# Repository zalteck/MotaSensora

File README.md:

# MotaSensora
Art monitoring for optimal conservation

This project was developed as the final degree job for my Telecommunications degree at the University of Granada. It implements from scratch a complete art monitoring system capable of measuring light, humidity, and temperature and ensuring that the values are kept in an acceptable range.

The system raises an alert in case any values get out of the safe range. It can also be escalated to control other devices in order to induce change to the monitored variables.

There are three different parts that form this project: Arduino code, Kicad files, and an Android app.

The Kicad files are used to build a PCB, used as an Arduino shield, that integrates the different sensors used in the project: Temperature, Humidity, and ambient light.

The Android app is completed and ready to install. With the app ArtSense, you will be able to communicate with the Arduino by Bluetooth, read the measurements, and know about the state of the ambient of the art piece, in terms of preventive conservation.

The Arduino code will manage the shield and read the sensors. It will also control Bluetooth connectivity and send the data to the Android device.
This is registered in zenodo:

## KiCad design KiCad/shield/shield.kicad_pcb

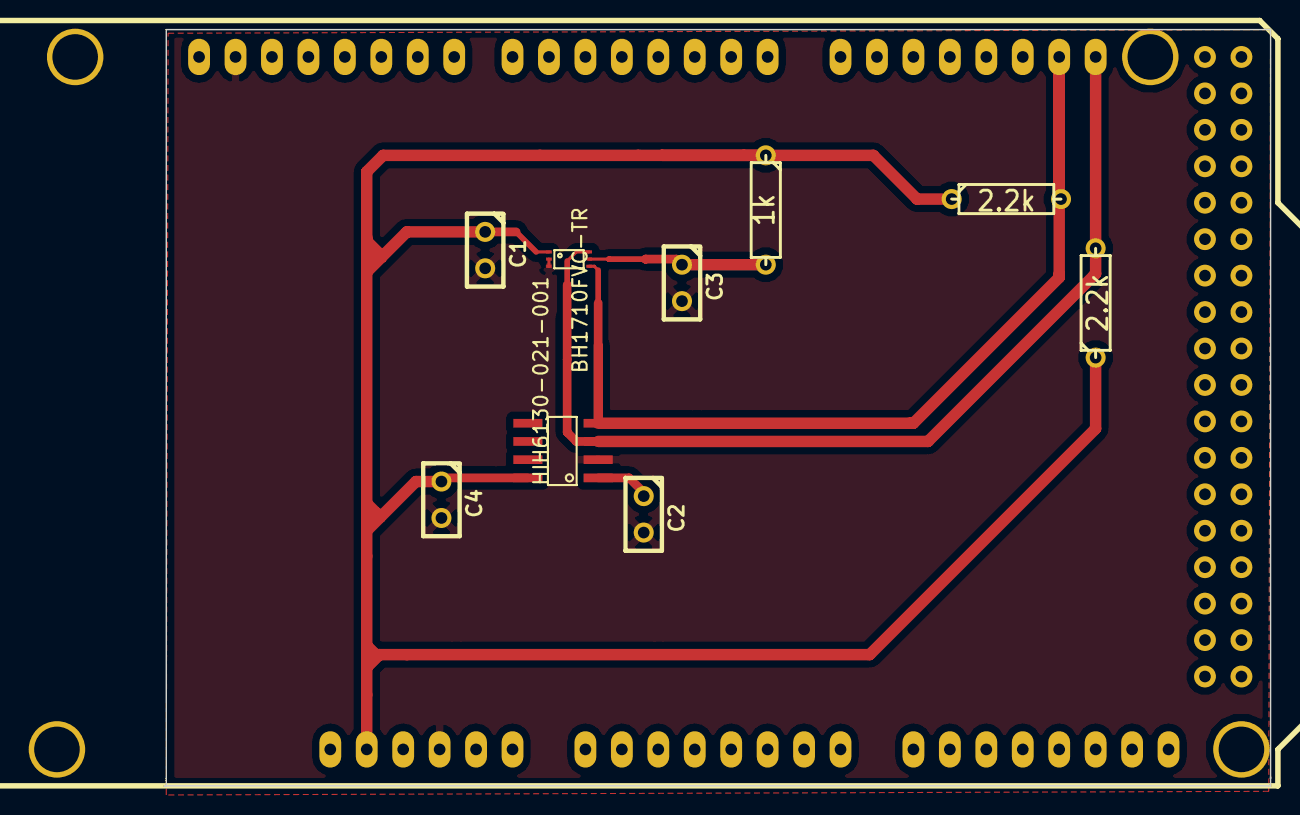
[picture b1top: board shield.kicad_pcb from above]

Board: 2 copper layers, 77.1 x 52.7 mm, 10 parts (0 on the bottom side), 6 nets.

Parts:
C1, C2: 0.1uF; C1
C3: 1uF; C1
C4: 0.22uF; C1
J1: BH1710FVC-TR; SensorLuz
J2: HIH6130-021-001; Humedad
R1: 1k; R3
R2, R3: 2.2k; R3
SHIELD1: ARDUINO_MEGA_SHIELD; ARDUINO MEGA SHIELD

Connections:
/DVI: C3.1, J1.5, R1.2
/SCL: J1.6, J2.3, R3.2, SHIELD1.21
/SDA: J1.4, J2.4, R2.2, SHIELD1.20
/Vcc: C1.1, C4.1, J1.1, J2.8, R1.1, R2.1, R3.1, SHIELD1.3V3
/Vcore: C2.1, J2.1
GND: C1.2, C2.2, C3.2, C4.2, J1.2, J1.3, J2.2, SHIELD1.GND1, SHIELD1.GND3

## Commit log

2015-02-09 :circus_tent: Added .gitattributes & .gitignore files
2015-02-09 Acercamiento a PCB
    Archivos de KiCad con un primer acercamiento al diseño de la PCB. Los
    footprint de los sensores no son validos.
2015-02-12 PCB con footprint de los sensores
    En esta versión. Los footprints son los que he realizado para adecuarse
    a los sensores de luz y humedad. Son muy pequeños. Dudo sobre el tamaño
    de pista.
2015-02-16 Revert "PCB con footprint de los sensores"
    This reverts commit 52ca6c0623bdd26822e73239bd101e933df6ce3b.
2015-02-16 Revert "Revert "PCB con footprint de los sensores""
    This reverts commit 291a17d979470ef3f704e2f34795666341a2ae8f.
2015-02-16 PCB con footprint de los sensores
2015-02-21 PCB shield para mota sensora
    Con planos de tierra en ambas capas, y tamaños de pista corregidos.
2015-02-24 Shield con correcciones
    No hay pistas en angulo recto.
    Una sola capa con plano de tierra hasta el borde
    Cambian los footprint de las resistencias
2015-02-24 Shield con correcciones
    Pistas aumentadas gradualmente
2015-02-24 Plano PCB en PDF
2015-03-05 Capas F.cu y F.Silks
    Planos en PDF del shield de sensores para arduino
2015-06-14 Codigo para Arduino
    Codigo para cargar en la placa Arduino y hacerlo funcionar como mota
    sensora
2015-06-14 Material relativo al PFC
    El contenido está repartido de la siguiente manera:
    -ArtSenseArduino: Codigo para la placa Arduino Mega ADK
    - KiCad: Archivos relativos a la fabricación de la PCB. Obsoletos
    - SensorControl: Código fuente de la app ArtSense para Android
2015-06-14 Codigo para Arduino
    Codigo para cargar en la placa Arduino Mega ADK para hacerla funcionar
    como mota sensora
2015-06-14 Archivos KiCad
    Material relativo a la fabricación de la primera PCB. Obsoleto
2015-06-14 App Android
    Codigo fuente de la app ArtSense para Android
2015-06-14 1er borrador
    Primer borrador de la memoria del PFC
2015-10-23 Create README.md
    General overview and description of the project MotaSensora
2015-10-23 Overview and description
    General overview and description of the project MotaSensora.
2023-11-24 Include doi
2023-11-24 Create LICENSE
2023-11-24 zenodo badge
2023-11-24 grammar correction
